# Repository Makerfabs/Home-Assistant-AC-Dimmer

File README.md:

# Home Assistant AC Dimmer

```c++
/*
Version:		V1.0
Author:			Makerfabs
Create Date:	2025/8/21
Note:

*/
```

## Intruduce

[Product Link](https://www.makerfabs.com/ac-dimmer-for-home-assistant.html)

[Wiki Link](https://wiki.makerfabs.com/How_to_use_AC_Dimmer_for_Home_Assistant.html)

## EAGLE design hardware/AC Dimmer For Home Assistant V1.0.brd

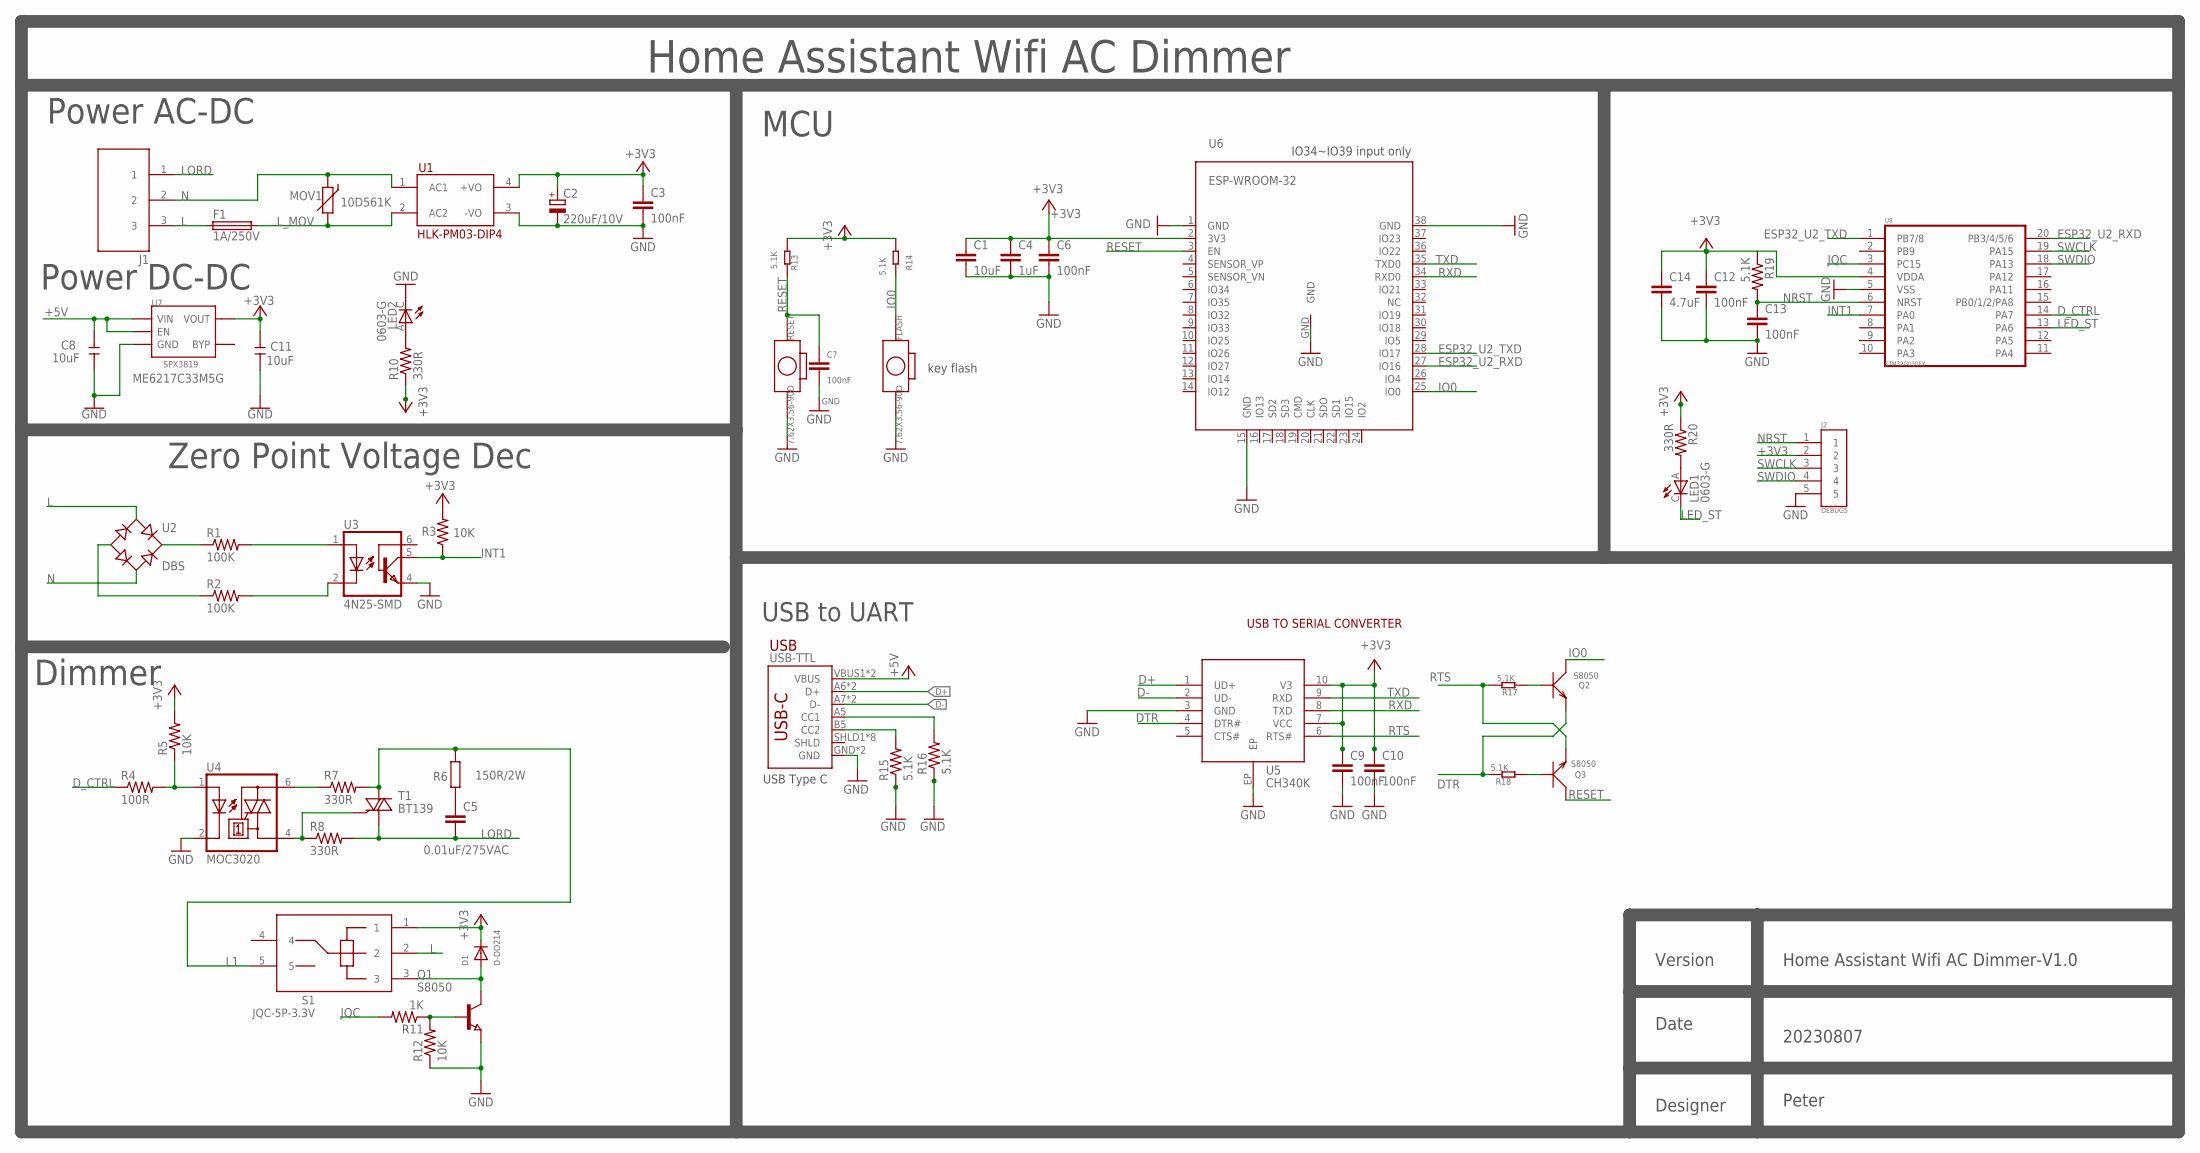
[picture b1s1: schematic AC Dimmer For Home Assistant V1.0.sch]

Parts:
C1, C8, C11: 10uF; C0603
C2: 220uF/10V; SMD-6.3*5
C3, C6, C7, C9, C10, C12, C13: 100nF; C0603
C4: 1uF; C0603
C5: 0.01uF/275VAC; XC10B6
C14: 4.7uF; C0603
D1: D-DO214; DO-214
F1: 1A/250V; PICOFUSE
FLASH: 7.62X3.56-90D; 2P-7.62X3.56-90D
J1: DBT50G-9.5-3P; THROUGH-HOLE-9.5
J2: DEBUG5; DEBUG*5
LED1, LED2: 0603-G; LED0603
MOV1: 10D561K; S10K11
Q1: S8050; SOT-23
Q2, Q3: S8050; SOT23
R1, R2: 100K; R0805
R3, R5, R12: 10K; R0603
R4: 100R; R0603
R6: 150R/2W; R-0617
R7, R8: 330R; R0805
R10, R20: 330R; R0603
R11: 1K; R0603
R13, R14, R15, R16, R17, R18, R19: 5.1K; R0603
RESET: 7.62X3.56-90D; 2P-7.62X3.56-90D
S1: JQC-5P-3.3V; JQC-5P-5V
T1: BT139; TO220
U1: HLK-PM03-DIP4; HLK-PM03
U2: DBS; DB-S
U3: 4N25-SMD; DIL6-SMD
U4: MOC3020; DIL6-SMD
U5: CH340K; ESOP-10-EP-150MIL
U6: ESP-WROOM-32
U7: SPX3819; SOT23-5
U8: STM32G030FX; TSSOP20
USB-TTL: USB_C5; USB-C-16P-5

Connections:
+3V3: C1.1, C2.+, C3.1, C4.1, C6.1, C9.1, C10.1, C11.2, C12.1, C14.1, D1.C, J2.2, R3.2, R5.2, R10.1, R13.2, R14.2, R19.1, R20.1, S1.1, U1.4 (+VO), U5.7 (VCC), U5.10 (V3), U6.2 (3V3), U7.5 (VOUT), U8.4 (VDDA)
+5V: C8.2, U7.1 (VIN), U7.3 (EN), USB-TTL.VBUS1 (VBUS), USB-TTL.VBUS2 (VBUS)
D+: U5.1 (UD+), USB-TTL.A6 (D+), USB-TTL.B6 (D+)
D-: U5.2 (UD-), USB-TTL.A7 (D-), USB-TTL.B7 (D-)
DTR: Q2.2 (E), R18.1, U5.4 (DTR#)
D_CTRL: R4.1, U8.14 (PA7)
ESP32_U2_RXD: U6.27 (IO16), U8.20 (PB3/4/5/6)
ESP32_U2_TXD: U6.28 (IO17), U8.1 (PB7/8)
GND: C1.2, C2.-, C3.2, C4.2, C6.2, C7.2, C8.1, C9.2, C10.2, C11.1, C12.2, C13.2, C14.2, FLASH.P$2 (2), J2.5, LED2.C, Q1.2 (E), R12.1, R15.1, R16.1, RESET.P$2 (2), U1.3 (-VO), U3.4 (EMI), U4.2 (C), U5.3 (GND), U5.EP, U6.1 (GND), U6.15 (GND), U6.38 (GND), U6.GND, U7.2 (GND), U8.5 (VSS), USB-TTL.GND, USB-TTL.GND2 (GND)
INT1: R3.1, U3.5 (COL), U8.7 (PA0)
IO0: FLASH.P$1 (1), Q2.3 (C), R14.1, U6.25 (IO0)
JQC: R11.2, U8.3 (PC15)
L: F1.1, J1.3, S1.2, U2.AC1
L1: R6.2, R7.2, S1.5, T1.A (A2)
LED_ST: LED1.C, U8.13 (PA6)
LORD: C5.2, J1.1, R8.2, T1.C (A1)
L_MOV: F1.2, MOV1.2, U1.2 (AC2)
N: J1.2, MOV1.1, U1.1 (AC1), U2.AC2
unnamed: LED1.A, R20.2
unnamed: Q1.1 (B), R11.1, R12.2
unnamed: D1.A, Q1.3 (C), S1.3
unnamed: R1.2, U3.1 (A)
unnamed: R2.1, U2.-
unnamed: R2.2, U3.2 (C)
unnamed: R7.1, U4.6 (A2)
unnamed: R8.1, T1.G, U4.4 (A1)
unnamed: C5.1, R6.1
unnamed: R4.2, R5.1, U4.1 (A)
unnamed: LED2.A, R10.2
unnamed: Q3.1 (B), R18.2
unnamed: Q2.1 (B), R17.2
unnamed: R1.1, U2.+
unnamed: R16.2, USB-TTL.A5 (CC1)
unnamed: R15.2, USB-TTL.B5 (CC2)
NRST: C13.1, J2.1, R19.2, U8.6 (NRST)
RESET: C7.1, Q3.3 (C), R13.1, RESET.P$1 (1), U6.3 (EN)
RTS: Q3.2 (E), R17.1, U5.6 (RTS#)
RXD: U5.8 (TXD), U6.34 (RXD0)
SWCLK: J2.3, U8.19 (PA15)
SWDIO: J2.4, U8.18 (PA13)
TXD: U5.9 (RXD), U6.35 (TXD0)

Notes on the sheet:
Home Assistant Wifi AC Dimmer
Power AC-DC
Zero Point Voltage Dec
Dimmer
MCU
Version
Date
Designer
Home Assistant Wifi AC Dimmer-V1.0
20230807
Peter
IO34~IO39 input only
key flash
USB to UART
USB TO SERIAL CONVERTER
USB
USB Type C
ME6217C33M5G
Power DC-DC

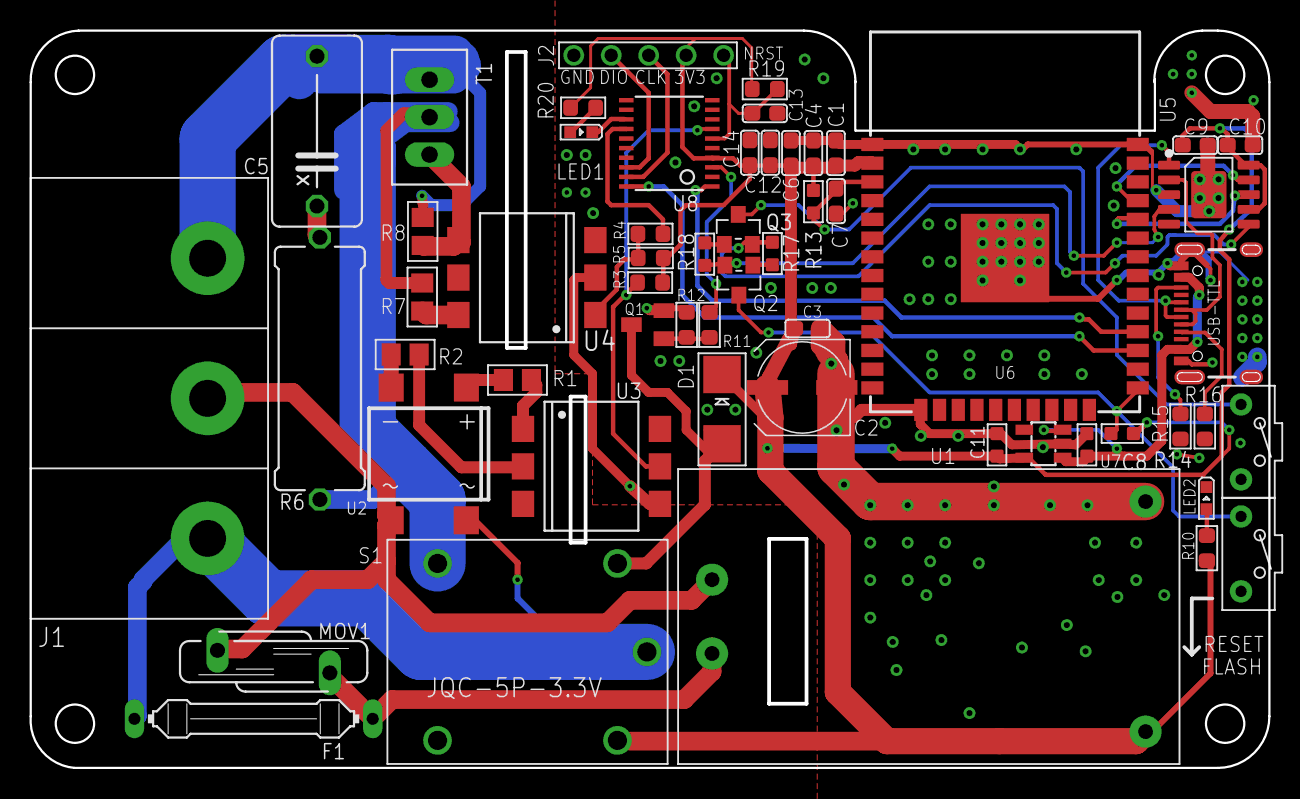
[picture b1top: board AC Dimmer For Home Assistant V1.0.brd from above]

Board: 2 copper layers, 83.9 x 49.9 mm, 57 parts (1 on the bottom side), 41 nets.

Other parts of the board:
U$6: MAKERFABS_0.3

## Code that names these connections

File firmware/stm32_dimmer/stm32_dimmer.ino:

#include <Arduino.h>
#include <HardwareTimer.h>

#define SCR_Pin PA7
#define RELAY_PIN PC15
#define LED_PIN PA6
#define ZCD_PIN PA0

#define DIM_MAX 10
#define DIM_MIN 90

#define AC_CTRL_OFF digitalWrite(SCR_Pin, LOW)
#define AC_CTRL_ON digitalWrite(SCR_Pin, HIGH)

#define RELAY_OFF digitalWrite(RELAY_PIN, LOW)
#define RELAY_ON digitalWrite(RELAY_PIN, HIGH)

#define LED_OFF digitalWrite(LED_PIN, HIGH)
#define LED_ON digitalWrite(LED_PIN, LOW)

unsigned char dim = 0;

volatile bool count_hz_flag = false;
volatile uint32_t count_hz = 0;
volatile unsigned long zc_samples[10];
volatile uint8_t zc_index = 0;
uint8_t dim_delay = 0;

uint32_t local_hz = 0;

HardwareTimer timer(TIM14);
HardwareSerial mySerial(PB7, PB6);
int led_flag = 0;



void onTimer() {
    if(zc_index < 10 && count_hz > 0) {
        zc_samples[zc_index++] = count_hz / 2;
        count_hz = 0;
    }
}


void setup()
{
    pinMode(LED_PIN, OUTPUT);
    pinMode(RELAY_PIN, OUTPUT);
    pinMode(SCR_Pin, OUTPUT);
    pinMode(ZCD_PIN, INPUT);
    LED_OFF;
    RELAY_OFF;
    AC_CTRL_OFF;

    mySerial.begin(115200);
    delay(1000);
    mySerial.println("Start");

    timer.setOverflow(1000000, MICROSEC_FORMAT);
    timer.attachInterrupt(onTimer);
    timer.setInterruptPriority(1, 0);
    timer.resume();

    attachInterrupt(ZCD_PIN, zero_cross_int, RISING); // CHANGE FALLING RISING
}

void loop()
{
    if (led_flag % 2 == 0)
        LED_ON;
    else
        LED_OFF;

    led_flag++;

    char c;
    String str = "";
    while (mySerial.available() > 0)
    {
        c = mySerial.read();
        if (c == '\n')
        {
            mySerial.println("Get line:");
            mySerial.println(str);
            at_explain(str);
        }
        else
            str = str + c;
    }


    if(zc_index == 10) {
        timer.pause();

        for (uint8_t i = 1; i < zc_index; i++)
        {
            unsigned long key = zc_samples[i];
            int j = i - 1;
            while (j >= 0 && zc_samples[j] > key)
            {
                zc_samples[j + 1] = zc_samples[j];
                j--;
            }
            zc_samples[j + 1] = key;
        }

        uint32_t sum = 0;
        for(uint8_t i = 1; i < zc_index - 1; i++) {
            sum += zc_samples[i];
        }
        local_hz = sum / (zc_index - 2);

        if(local_hz > 47 && local_hz < 53) {
            dim_delay = 100;
        } else if(local_hz >= 57 && local_hz < 63) {
            dim_delay = 80;
        }
    }

    delay(1000);
}

// AT D50
void at_explain(String command)
{
    if (command.startsWith("AT"))
    {
        int var_1 = 0;

        sscanf(command.c_str(), "AT D%d", &var_1);
        mySerial.println(var_1);

        set_power(var_1);
    }
}

void set_power(int level)
{
    dim = map(level, 0, 100, DIM_MIN, DIM_MAX);
    if (level == 0)
    {
        RELAY_OFF;
    }
    else
        RELAY_ON;
}

void zero_cross_int() // function to be fired at the zero crossing to dim the light
{

    if(zc_index < 10) {
        count_hz++;
    }

    if (dim <= DIM_MAX)
        return;
    // if (dim >= DIM_MIN)
    //     return;

    AC_CTRL_OFF;

    int dimtime = (dim_delay * dim);
    delayMicroseconds(dimtime); // Off cycle
    AC_CTRL_ON;                 // triac firing
    // delayMicroseconds(500);     // triac On propagation delay
    // triac Off
}

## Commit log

2025-08-21 fix yaml
2025-10-31 fix 60hz error
2025-11-24 add .gitignore

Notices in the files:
parts and their libraries:
SparkFun-Aesthetics: Licensing: Creative Commons ShareAlike 4.0 International - https://creativecommons.org/licenses/by-sa/4.0
